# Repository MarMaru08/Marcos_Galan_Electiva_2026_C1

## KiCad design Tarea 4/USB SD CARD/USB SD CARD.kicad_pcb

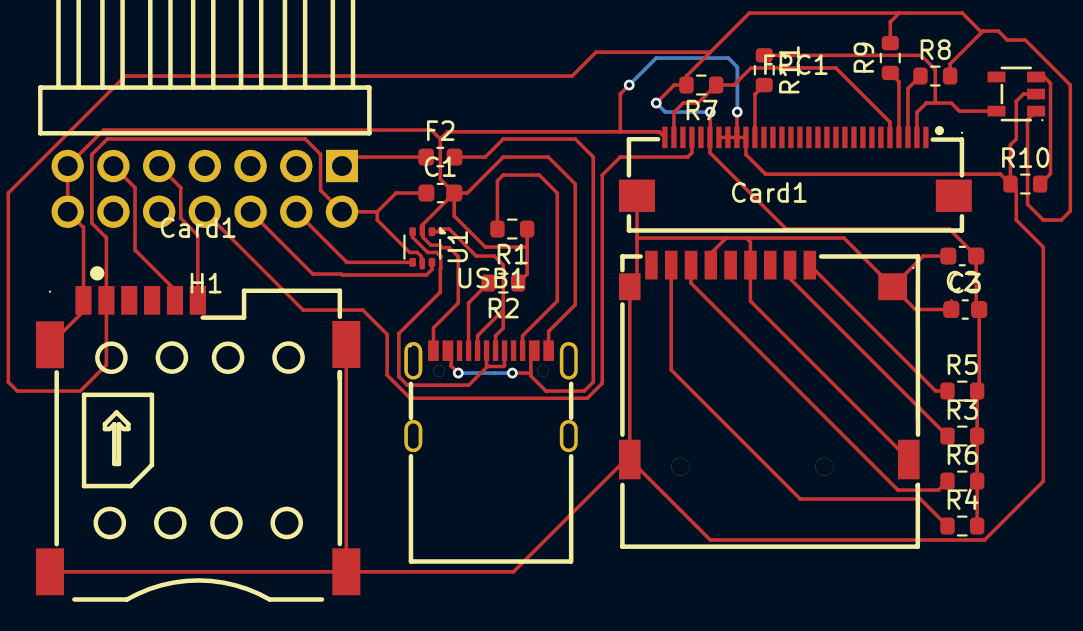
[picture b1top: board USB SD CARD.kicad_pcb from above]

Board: 2 copper layers, 22 parts (0 on the bottom side), 23 nets.

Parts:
C1, C2: 100nF; C_0603_1608Metric
C3: 10uF; C_0603_1608Metric
Card1: SMC-202-6; SIM-SMD_SMC-202-6
Card1#2: TF-115; TF-SMD_TF-115
F2: Polyfuse_Small; Fuse_0603_1608Metric
FPC1: FPC-05FB-30PH20; FPC-SMD_30P-P0.50_FPC-05FB-30PH20
H1: PZ254R-12-14P; HDR-TH_14P-P2.54-H-M-R2-C7-S2.54
R1, R2, R10, R11: 5.1K; R_0603_1608Metric
R3, R4, R5, R6, R7, R8, R9: 10K; R_0603_1608Metric
U1: USBLC6-2P6; SOT-666
U2: MT9700-N; SOT-23-5_L2.9-W1.6-P0.95-LS2.9-BL
USB1: LCK-TCF809-L117YL-G1; USB-C-SMD_LCK-TCF809-L117YL-G1

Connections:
3.3V: C1.1, C2.1, C3.2, Card1.C1 (VCC), FPC1.25, H1.2, R3.2, R4.2, R5.2, R6.2, R7.2, R8.2, R9.2, U1.5 (VBUS), U2.1 (VOUT)
5V: F2.1, H1.1
D+: U1.3 (I/O2), USB1.A6 (DP1), USB1.B6 (DP2)
D-: U1.1 (I/O1), USB1.A7 (DN1), USB1.B7 (DN2)
GND: C1.2, C2.2, C3.1, Card1.7 (GND), Card1.8 (GND), Card1.9 (GND), Card1.10 (GND), Card1.C5 (GND), Card1#2.4 (VDD), Card1#2.6 (VSS), Card1#2.10 (SHELL), Card1#2.11 (SHELL), Card1#2.12 (SHELL), Card1#2.13 (SHELL), FPC1.21, FPC1.22, FPC1.23, FPC1.24, FPC1.30, FPC1.31, H1.13, H1.14, R1.1, R2.1, R10.1, U1.2 (GND), U2.2 (GND), USB1.A1B12 (GND), USB1.B1A12 (GND)
GPIO1: Card1.C7 (I/O), H1.11
IM1: FPC1.4, R9.1
IM2: FPC1.3, R8.1
LED: FPC1.20, R11.2
unnamed: Card1#2.8 (DAT1), R4.1
unnamed: Card1#2.1 (DAT2), R5.1
unnamed: F2.2, USB1.A4B9 (VBUS), USB1.B4A9 (VBUS)
unnamed: R10.2, U2.3 (SET)
unnamed: R2.2, USB1.A5 (CC1)
unnamed: R1.2, USB1.B5 (CC2)
SD_CS: Card1#2.2 (CD/DAT3), R3.1
SPI_MISO: Card1#2.7 (DAT0), R6.1
USB+: H1.4, U1.4 (I/O2)
USB-: H1.6, U1.6 (I/O1)
VDD: FPC1.2, R11.1, U2.5 (VIN)
clk: Card1.C3 (CLK), H1.9
idc_SDA: FPC1.27, H1.8
reset: FPC1.5, FPC1.29, R7.1

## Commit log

2026-03-23 primer commit
2026-04-14 Segundo commit
2026-04-14 Tercer commit del proyecto
2026-04-24 Mi cuarto commit de PLC4UNI
2026-04-24 mi quinto commit
